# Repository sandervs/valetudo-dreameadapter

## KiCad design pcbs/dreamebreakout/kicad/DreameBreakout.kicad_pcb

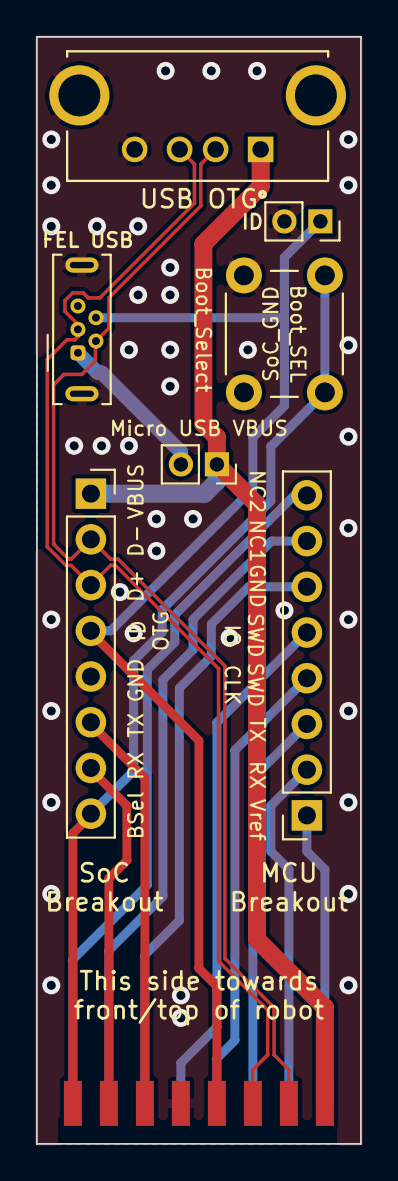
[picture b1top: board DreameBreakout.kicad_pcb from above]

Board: 2 copper layers, 18.0 x 61.5 mm, 9 parts (1 on the bottom side), 17 nets.

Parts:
J1.1: To Robot SoC; DGI_8_SMDPADS
J1.2: To Robot MCU; DGI_8_SMDPADS
J2: SoC Breakout; PinSocket_1x08_P2.54mm_Vertical
J3: MCU Breakout; PinSocket_1x08_P2.54mm_Vertical
J4: SoC_FEL_USB; USB_Micro-B_Wuerth_614105150721_Vertical
J5: OTG_USB; ONSHORE_USB-A1VSB6
JP1: JP_USB_VBUS; PinSocket_1x02_P2.00mm_Vertical
JP2: JP_USB_OTG_ID; PinSocket_1x02_P2.00mm_Vertical
SW1: SoC_Boot_SEL_BTN; SW_PUSH_6mm

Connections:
Boot_SEL: J1.1.1, J2.8, SW1.2
GND: J1.1.4, J2.5, J4.5 (GND_5), J4.SH (Shield_6), J5.4 (GND), J5.S1, J5.S2, JP2.2 (B), SW1.1
MCU_GND: J1.2.6, J3.6
MCU_NC1: J1.2.7, J3.7
MCU_NC2: J1.2.8, J3.8
MCU_RX: J1.2.2, J3.2
MCU_SWCLK: J1.2.4, J3.4
MCU_SWDIO: J1.2.5, J3.5
MCU_TX: J1.2.3, J3.3
MCU_Vref: J1.2.1, J3.1
SoC_RX: J1.1.2, J2.7
SoC_TX: J1.1.3, J2.6
SoC_USB_OTG_ID: J1.1.5, J2.4, J4.4 (ID_4), JP2.1 (A)
USB_D+: J1.1.6, J2.3, J4.3 (D+_3), J5.3 (D+)
USB_D-: J1.1.7, J2.2, J4.2 (D-_2), J5.2 (D-)
USB_VBUS: J4.1 (VBUS_1), JP1.2 (B)
VBUS: J1.1.8, J2.1, J5.1 (VBUS), JP1.1 (A)
